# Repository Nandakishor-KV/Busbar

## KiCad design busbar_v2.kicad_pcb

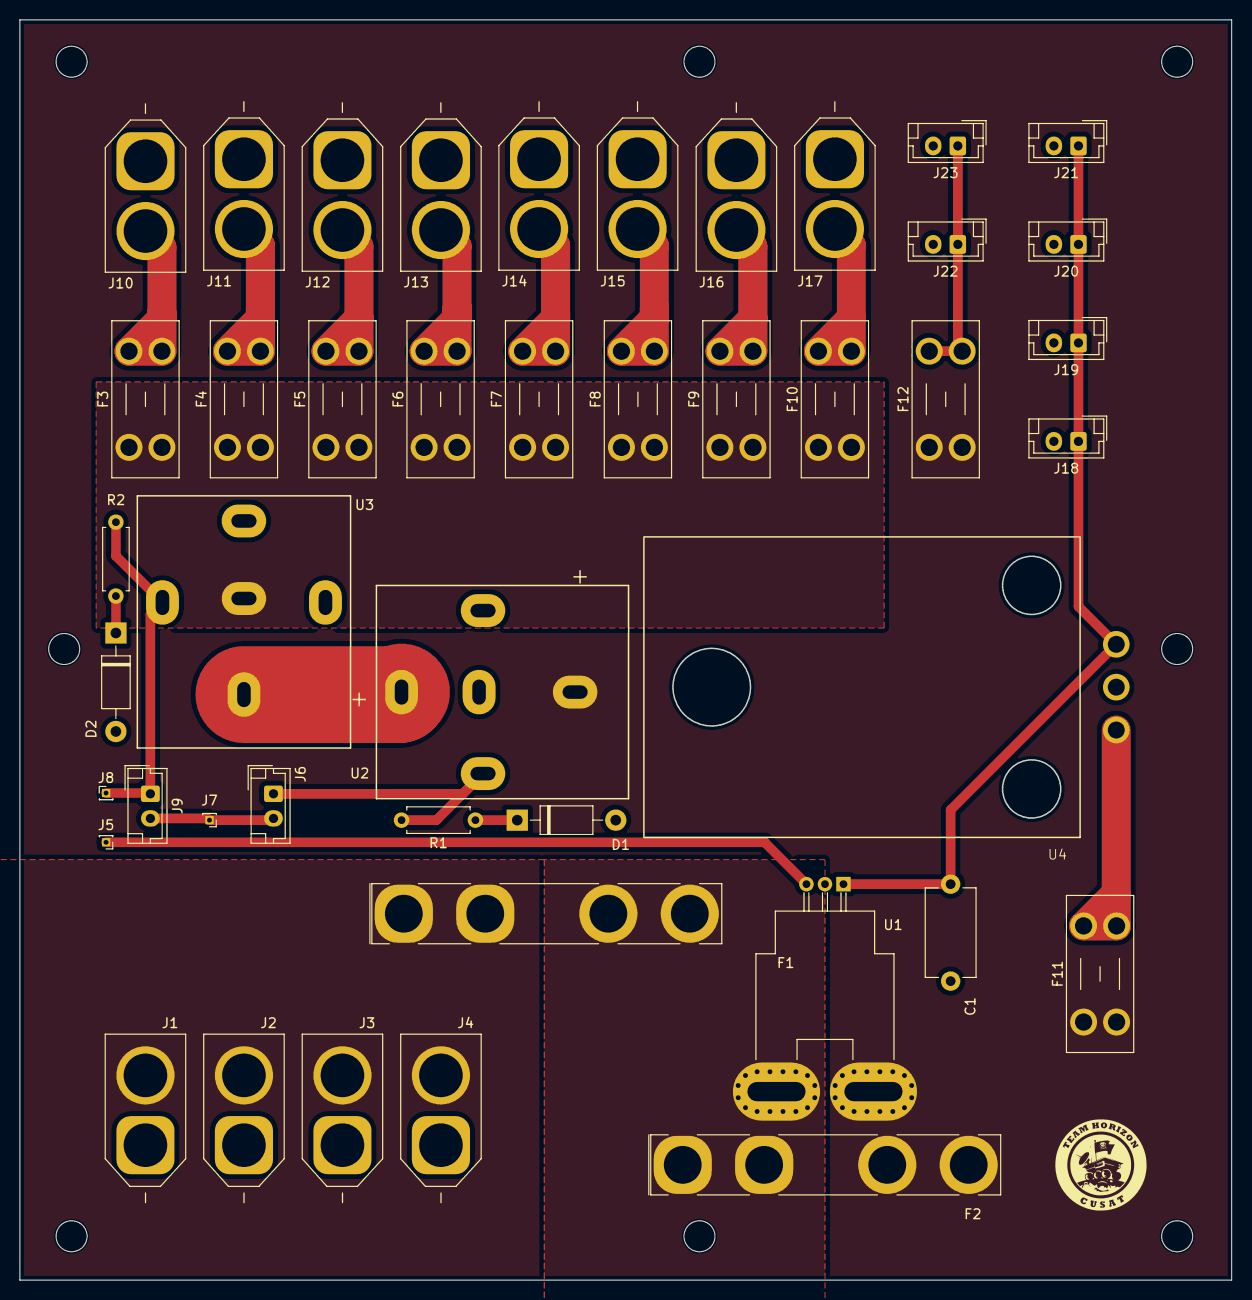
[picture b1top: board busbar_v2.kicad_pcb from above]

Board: 2 copper layers, 125.0 x 130.0 mm, 44 parts (0 on the bottom side), 23 nets.

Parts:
C1: C; C_Disc_D9.0mm_W5.0mm_P10.00mm
D1, D2: 1N4001; D_DO-41_SOD81_P10.16mm_Horizontal
F1, F2: ?; Fuseholder_Keystone_3555-2
F3, F4, F5, F6, F7, F8, F9, F10, F11, F12: ?; Fuseholder_Blade_Mini_Keystone_3568
J1, J2, J3, J4, J10, J11, J12, J13, J14, J15, J16, J17: Conn_01x02_Socket; AMASS_XT60-F_1x02_P7.20mm_Vertical - Round Pads
J5: Conn_01x01_Pin; PinHeader_1x01_P1.00mm_Vertical
J6: NC; JST_EH_B2B-EH-A_1x02_P2.50mm_Vertical
J7, J8: ES; PinHeader_1x01_P1.00mm_Vertical
J9: NO; JST_EH_B2B-EH-A_1x02_P2.50mm_Vertical
J18, J19, J20, J21, J22, J23: Conn_01x02_Socket; JST_EH_B2B-EH-A_1x02_P2.50mm_Vertical
R1, R2: R; R_Axial_DIN0207_L6.3mm_D2.5mm_P7.62mm_Horizontal
U1: ACS758xCB-050U-PFF; Allegro_CB_PFF
U2, U3: CB1-P-12V; RELAY_CB1-P_PAN
U4: buck_5V

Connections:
+12V: F2.2, F11.1, F12.1, U1.5 (IP-), U2.1 (30)
/12V OUT: F3.1, F4.1, F5.1, F6.1, F7.1, F8.1, F9.1, F10.1, U3.5 (87a)
/+5V OUT: C1.1, J18.1, J19.1, J20.1, J21.1, U1.1 (VCC), U4.3 (5V_OUT)
/+IN: F1.1, J1.1, J2.1, J3.1, J4.1
/CM: F1.2, F2.1, U1.4 (IP+)
/Relay Feedback: J8.1, J9.1, R2.2, U3.2 (86)
/Relay Signal: J6.2, J7.1, J9.2
GND: C1.2, D1.2 (A), D2.2 (A), J1.2, J2.2, J3.2, J4.2, J10.2, J11.2, J12.2, J13.2, J14.2, J15.2, J16.2, J17.2, J18.2, J19.2, J20.2, J21.2, J22.2, J23.2, U1.2 (GND), U2.4 (85), U3.4 (85), U4.2 (GND)
unnamed: D1.1 (K), R1.1
unnamed: D2.1 (K), R2.1
unnamed: J5.1, U1.3 (VIOUT)
unnamed: J6.1, R1.2, U2.2 (86)
unnamed: F3.2, J10.1
unnamed: F4.2, J11.1
unnamed: F5.2, J12.1
unnamed: F6.2, J13.1
unnamed: F7.2, J14.1
unnamed: F8.2, J15.1
unnamed: F9.2, J16.1
unnamed: F10.2, J17.1
unnamed: F12.2, J22.1, J23.1
unnamed: U2.3 (87), U3.1 (30)
unnamed: F11.2, U4.1 (12V_IN)
